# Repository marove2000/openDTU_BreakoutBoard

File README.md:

# OpenDTU Breakout Board

This is a fully comaptible Breakout Board for the [OpenDTU](https://github.com/tbnobody/OpenDTU/) Project. With the opendtu breakout board and the opendtu software, you can read out, control and process Hoymiles inverters. In addition, the current energy yield is shown directly on a display.

This PCB has been designed together with the developers and is fully compatible. New features will of course always be added immediately ;).

### Parts List

| Quantity | Name | Description | Label/Color Code |
|----------|------|-------------|------------------|
| 1     | U1   | ESP32       | ESP32-WROOM32         |
| 1     | U2   | Wireless module   | ML01DP5               |
| 2     | D1,D2 | 3mm green LED |                      |
| 1     | C1   | 10µF capacitor |                      |
| 2     | C2   | 100nF ceramic capacitor | 104                |
| 1     | J1   | 4x L-shaped pin header |                      |
| 2     | U1   | 1x19 pin female header |                      |
| 1     |      | 4-way cable |                      |
| 1     | R1,R2 | 68Ω resistor |  |
| 1     | R3   | 390Ω resistor |  |
| 1     |      | PCB (Printed Circuit Board) |                      |
| 6     |      | Optional: M2x6 screw |                      |
| 2     |      | Optional: 3D-printed case parts |                      |
| 2     |      | Not included: Toothpick |                      |
| 1     |      | Not included: Micro-USB cable |                      |

### Purchase a Soldering Kit

If you don't want to source the PCBs and components yourself, you can also buy a soldering kit directly from the online shop at blinkyparts.com: [https://shop.blinkyparts.com/de/OpenDTU-Breakoutboard-Dein-Auswertung-fuer-deine-Balkonsolaranlage/blink237542](https://shop.blinkyparts.com/de/OpenDTU-Breakoutboard-Dein-Auswertung-fuer-deine-Balkonsolaranlage/blink237542)

### Manual
You can find the manual and pictures of every build step here: [https://github.com/Binary-Kitchen/SolderingTutorial/tree/master/OpenDTU_Breakout](https://github.com/Binary-Kitchen/SolderingTutorial/tree/master/OpenDTU_Breakout)

## Case

You cand find the Case here: [https://www.printables.com/de/model/441037-opendtu-breakoutboard-case](https://www.printables.com/de/model/441037-opendtu-breakoutboard-case)

### Copyright and Authorship

- Board: [CC-BY-NC-SA 4.0](https://creativecommons.org/licenses/by-nc-sa/4.0/) - Noby, Jan and Timo @ [blinkyparts.com](https://shop.blinkyparts.com)
- Code: [GPLv2](https://www.gnu.org/licenses/old-licenses/gpl-2.0.html) - [tbnobody](https://github.com/tbnobody/OpenDTU)
- Manual (TeX): [LPPL](https://www.latex-project.org/lppl.txt) - [Marei Peischl](https://peitex.de)
- Manual (pdf): [CC-BY-SA 4.0](https://creativecommons.org/licenses/by-sa/4.0/) - [Binary Kitchen e.V.](https://www.binary-kitchen.de)

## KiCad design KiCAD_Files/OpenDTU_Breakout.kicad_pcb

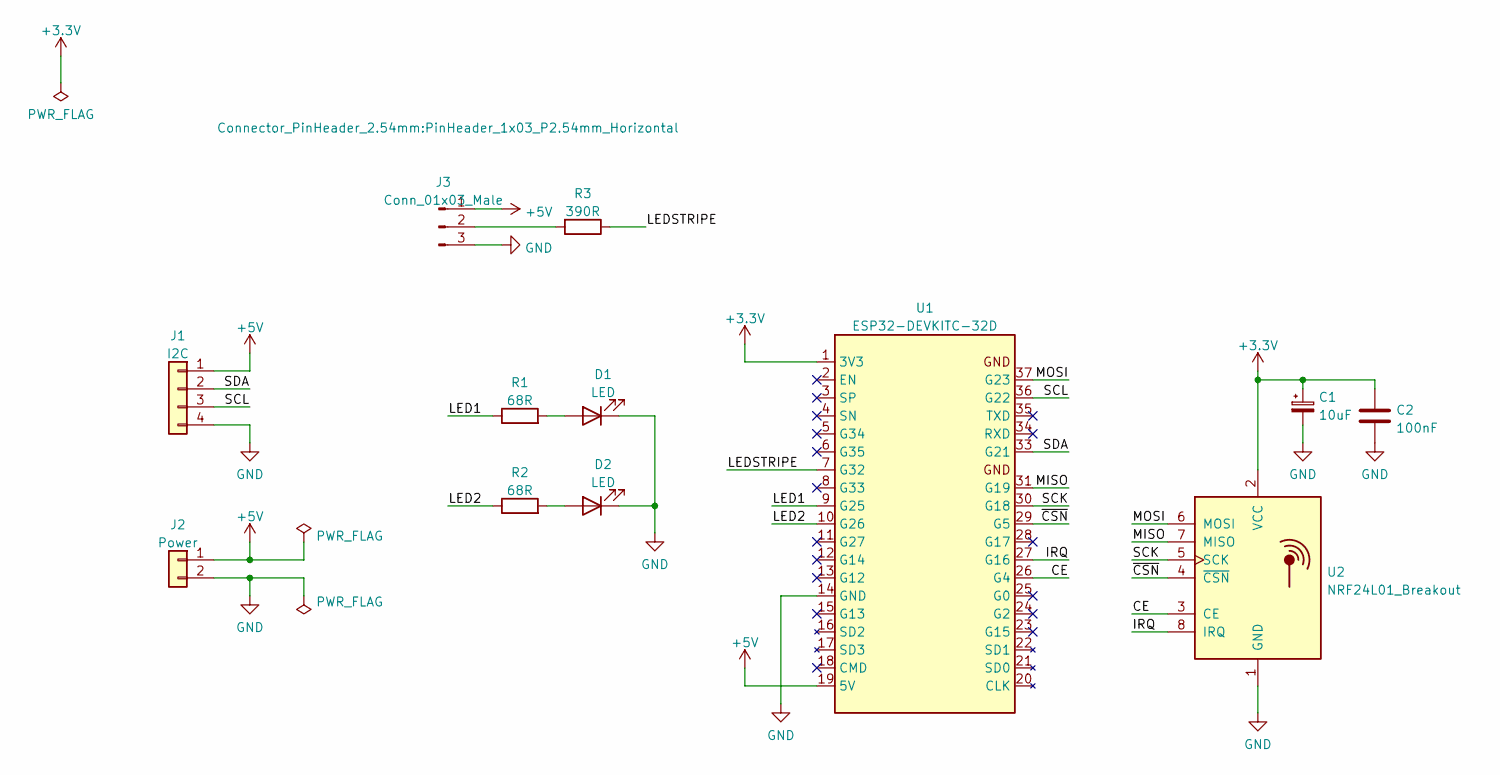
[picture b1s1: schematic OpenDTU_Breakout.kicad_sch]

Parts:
C1: 10uF; CP_Radial_D5.0mm_P2.00mm
C2: 100nF; C_Disc_D4.3mm_W1.9mm_P5.00mm
D1, D2: LED; LED_D3.0mm
J1: I2C; PinHeader_1x04_P2.54mm_Horizontal
J2: Power; JST_EH_S2B-EH_1x02_P2.50mm_Horizontal
J3: Conn_01x03_Male; PinHeader_1x03_P2.54mm_Horizontal
R1, R2: 68R; R_Axial_DIN0207_L6.3mm_D2.5mm_P10.16mm_Horizontal
R3: 390R; R_Axial_DIN0207_L6.3mm_D2.5mm_P10.16mm_Horizontal
U1: ESP32-DEVKITC-32D; ESP32-NodeMCU_WROOM_32; PARTREV 4
U2: NRF24L01_Breakout; nRF24L01+PA+LNA_Breakout

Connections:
+3.3V: C1.1, C2.1, U1.1 (3V3), U2.2 (VCC)
+5V: J1.1, J2.1, J3.1, U1.19 (5V)
/CE: U1.26 (G4), U2.3 (CE)
/IRQ: U1.27 (G16), U2.8 (IRQ)
/LED1: R1.1, U1.9 (G25)
/LED2: R2.1, U1.10 (G26)
/LEDSTRIPE: R3.1, U1.7 (G32)
/MISO: U1.31 (G19), U2.7 (MISO)
/MOSI: U1.37 (G23), U2.6 (MOSI)
/SCK: U1.30 (G18), U2.5 (SCK)
/SCL: J1.3, U1.36 (G22)
/SDA: J1.2, U1.33 (G21)
/~CSN: U1.29 (G5), U2.4 (~CSN)
GND: C1.2, C2.2, D1.1 (K), D2.1 (K), J1.4, J2.2, J3.3, U1.14 (GND), U1.32 (GND), U1.38 (GND), U2.1 (GND)
unnamed: D1.2 (A), R1.2
unnamed: D2.2 (A), R2.2
unnamed: J3.2, R3.2

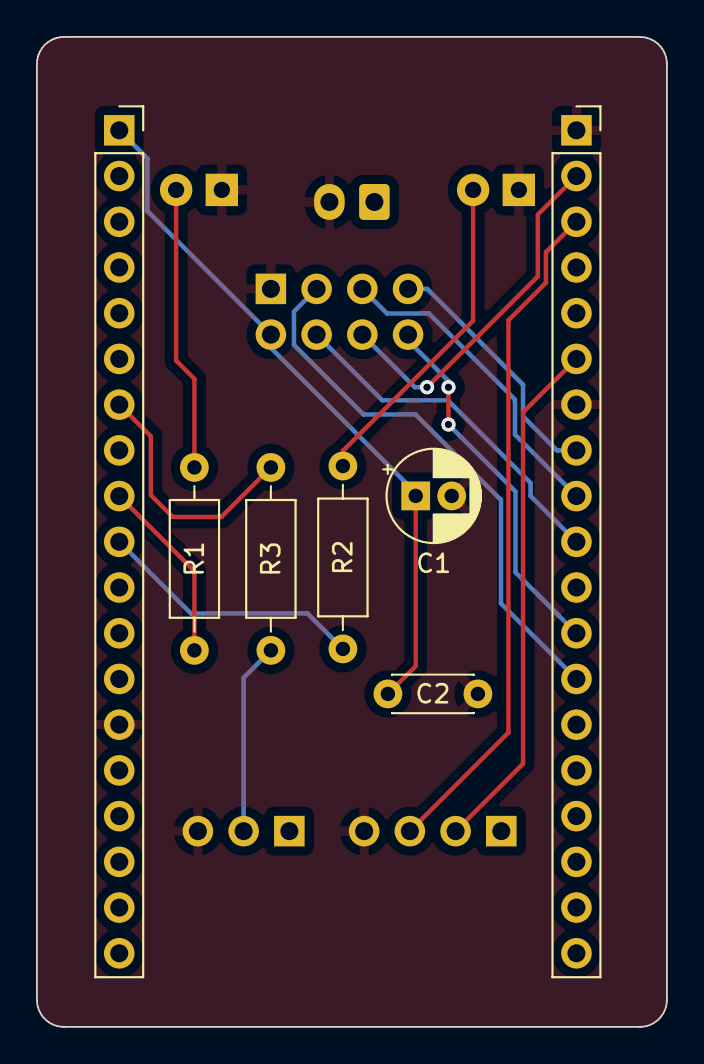
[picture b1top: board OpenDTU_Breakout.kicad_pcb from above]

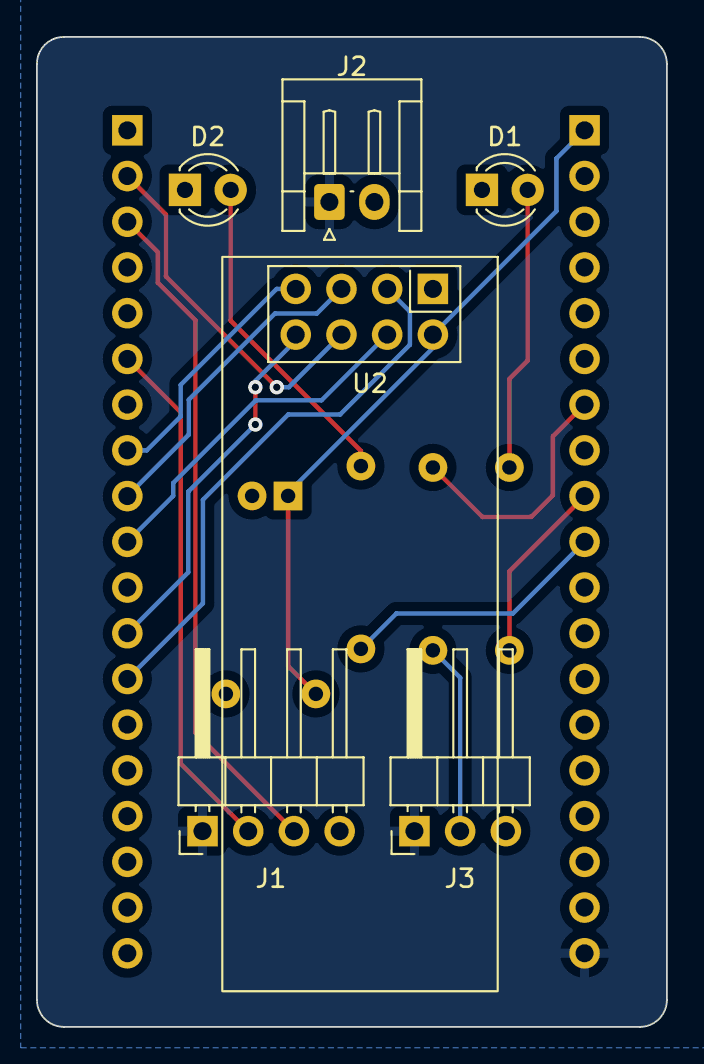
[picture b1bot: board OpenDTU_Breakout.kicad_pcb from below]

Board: 2 copper layers, 35.0 x 55.0 mm, 12 parts (6 on the bottom side), 17 nets.

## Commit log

2023-04-16 added gitignore
2023-04-16 initial kicad commit
2023-04-16 added gerber files for REV2
2023-04-16 added CC-BY-SA 4.0 licence file
2023-04-16 added readme
2023-04-16 added case to readme
2023-04-19 flipped and rotated J1 and J3
2023-04-19 updated ibom
2023-04-19 generated new gerber files for REV3
